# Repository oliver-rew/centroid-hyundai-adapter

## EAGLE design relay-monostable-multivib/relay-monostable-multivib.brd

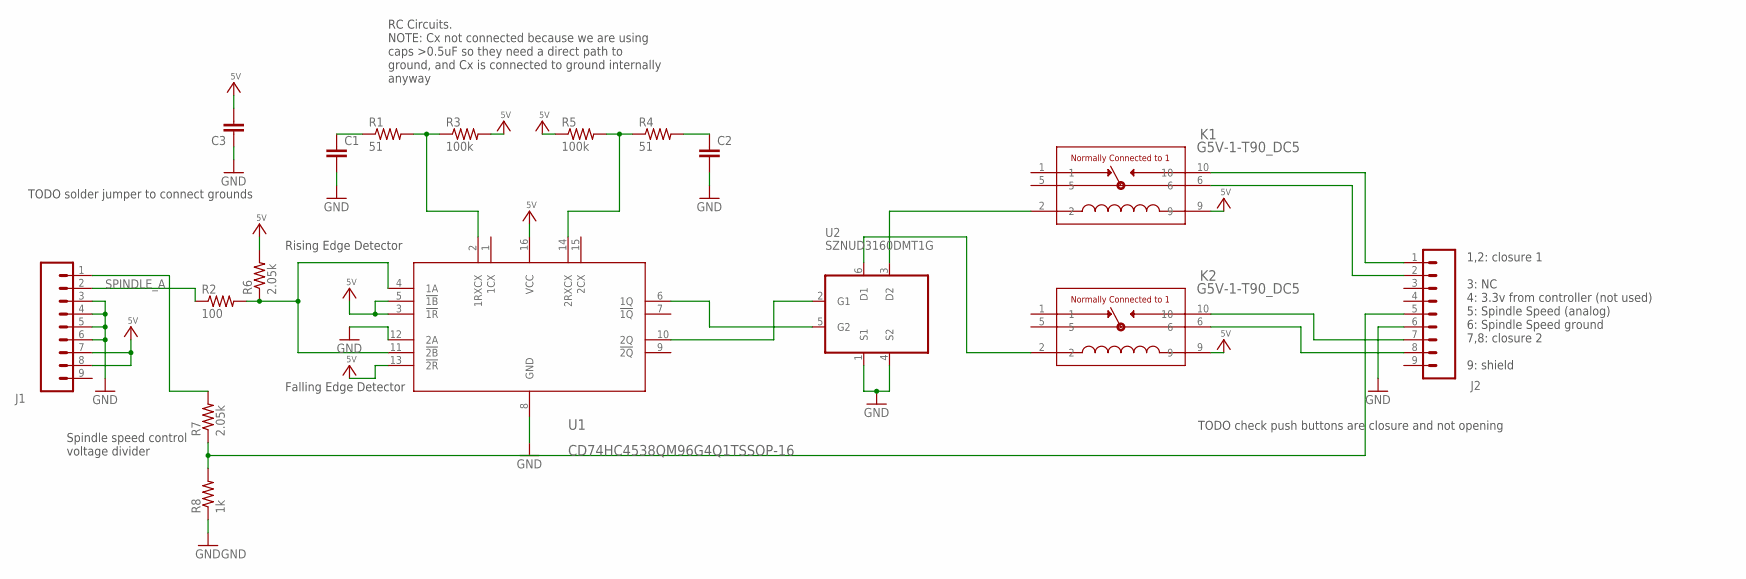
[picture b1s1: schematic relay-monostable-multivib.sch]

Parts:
C1, C2, C3: C-EU1206-A; 1206-A
J1, J2: CONN_09LONGPADS; 1X09_LONGPADS
K1, K2: G5V-1-T90_DC5; RELAY_G5V-1_OMR
R1, R4: 51; 1206-A
R2: 100; 1206-A
R3, R5: 100k; 1206-A
R6, R7: 2.05k; 1206-A
R8: 1k; 1206-A
U1: CD74HC4538QM96G4Q1TSSOP-16; TSSOP16
U2: SZNUD3160DMT1G; SC74_6

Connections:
5V: C3.2, J1.7, J1.8, K1.9, K2.9, R3.2, R5.1, R6.2, U1.3 (!1R), U1.5 (!1B), U1.13 (!2R), U1.16 (VCC)
GND: C1.2, C2.2, C3.1, J1.3, J1.4, J1.5, J1.6, J2.6, R8.1, U1.8 (GND), U1.12 (2A), U2.1 (S1), U2.4 (S2)
unnamed: K2.2, U2.6 (D1)
unnamed: U1.6 (1Q), U2.5 (G2)
unnamed: U1.10 (2Q), U2.2 (G1)
unnamed: K1.2, U2.3 (D2)
unnamed: J2.5, R7.1, R8.2
unnamed: R1.2, R3.1, U1.2 (1RXCX)
unnamed: C1.1, R1.1
unnamed: R4.1, R5.2, U1.14 (2RXCX)
unnamed: C2.1, R4.2
unnamed: R2.2, R6.1, U1.4 (1A), U1.11 (!2B)
unnamed: J1.2, R2.1
unnamed: J2.2, K1.6
unnamed: J2.7, K2.10
unnamed: J2.8, K2.6
unnamed: J2.1, K1.10
SPINDLE_A: J1.1, R7.2

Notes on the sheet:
Rising Edge Detector
TODO solder jumper to connect grounds
Falling Edge Detector
RC Circuits. NOTE: Cx not connected because we are using caps >0.5uF so they need a direct path to ground, and Cx is connected to ground internally anyway
TODO check push buttons are closure and not opening
Spindle speed control voltage divider
1,2: closure 1 3: NC 4: 3.3v from controller (not used) 5: Spindle Speed (analog) 6: Spindle Speed ground 7,8: closure 2 9: shield

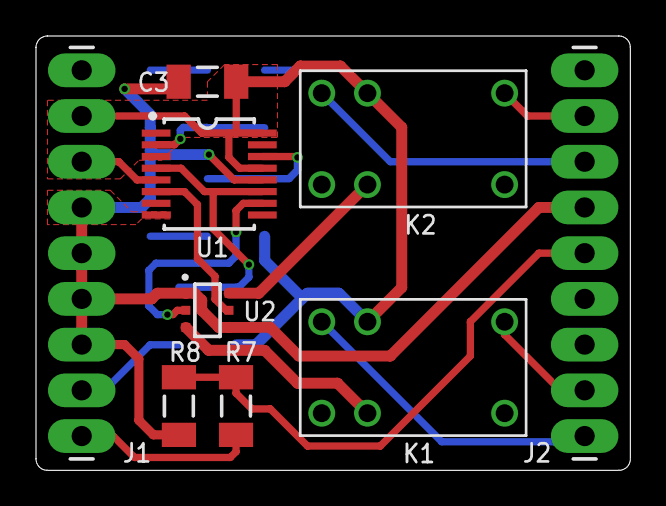
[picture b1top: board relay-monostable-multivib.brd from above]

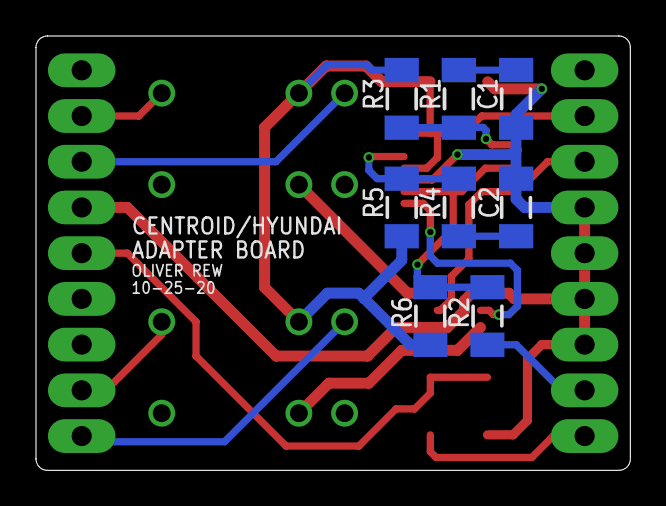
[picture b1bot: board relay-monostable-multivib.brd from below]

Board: 2 copper layers, 33.0 x 24.1 mm, 17 parts (8 on the bottom side), 18 nets.

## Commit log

2020-10-26 added finished board

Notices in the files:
parts and their libraries:
SparkFun-Connectors: Licensing: Creative Commons ShareAlike 4.0 International - https://creativecommons.org/licenses/by-sa/4.0
COPYRIGHT: Copyright (C) 2018 Accelerated Designs. All rights reserved
